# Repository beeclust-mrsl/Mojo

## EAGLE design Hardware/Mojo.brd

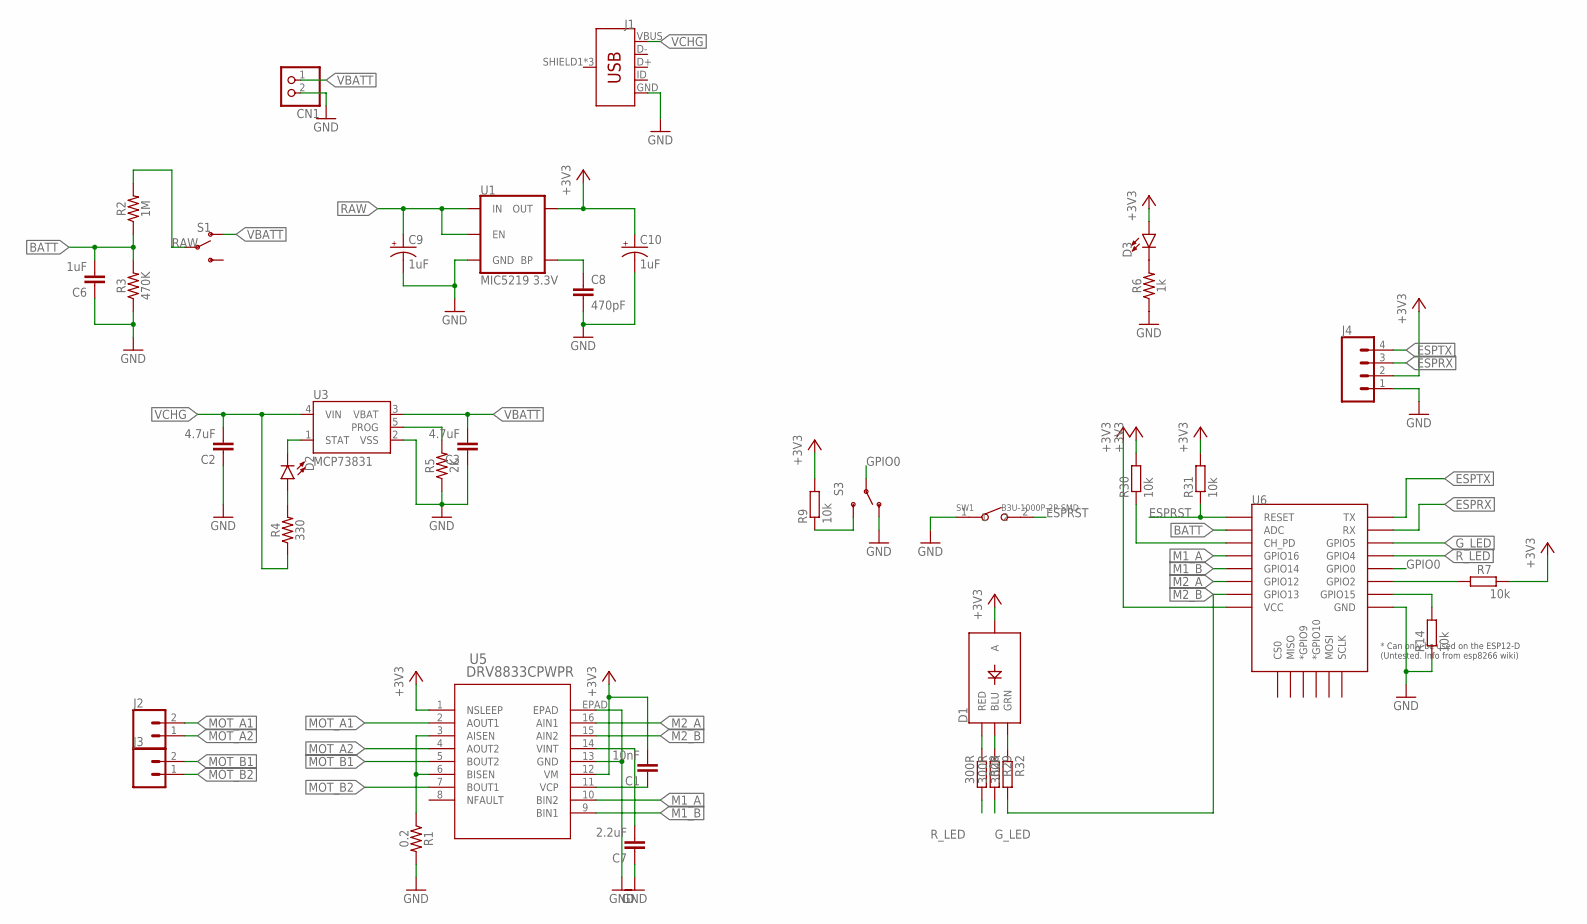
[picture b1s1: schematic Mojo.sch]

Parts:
C1: 10nF; C0603
C2, C3: 4.7uF; C0603
C6: 1uF; C0603
C7: 2.2uF; C0603
C8: 470pF; 0603
C9, C10: 1uF; EIA3216
CN1: JST_2PIN-THM-RA; JST-PH-2-THM-RA
D1: LED-RGB-CASMD; LED-TRICOLOR-SMD
D2, D3: LED0603; LED-0603
J1: USB_MICRO-BREDUCED_PASTE; USB-B-MICRO-SMD_RED_PASTE
J2, J3: CONN_02; 1X02
J4: CONN_04; 1X04
R1: 0.2; 0603
R2: 1M; 0603
R3: 470K; 0603
R4: 330; 0603
R5: 2K; 0603
R6: 1k; 0603
R7, R9, R14, R30, R31: 10k; R0603
R28, R29, R32: 300R; R0603
S1: SWITCH-SPDT-SMD-RIGHT-ANGLE; SWITCH_SPST_SMD_A
S3: SWITCH-SPDT-SMD-A; SWITCH-SPST-SMD-A
SW1: B3U-1000P-2P-SMD; SW2-2.6-3.0X2.5X1.2+0.4MM
U1: MIC5219 3.3V; SOT23-5
U3: MCP73831; SOT23-5
U5: DRV8833CPWPR; PWP16_2P31X2P46
U6: ESP12ESMD; ESP12E-SMD

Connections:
+3V3: C1.2, C10.+, D1.A, D3.A, J4.2, R7.2, R9.2, R30.2, R31.2, U1.5 (OUT), U5.1 (NSLEEP), U5.12 (VM), U6.VCC
BATT: C6.2, R2.1, R3.2, U6.ADC
ESPRST: R31.1, SW1.2, U6.RESET
ESPRX: J4.3, U6.RXD0 (RX)
ESPTX: J4.4, U6.TXD0 (TX)
GND: C2.1, C3.1, C6.1, C7.1, C8.2, C9.-, C10.-, CN1.2 (1), J1.GND, J4.1, R1.2, R3.1, R5.1, R6.1, R14.1, S3.1 (O), SW1.1, U1.2 (GND), U3.2 (VSS), U5.13 (GND), U5.EPAD, U6.GND
GPIO0: S3.2, U6.GPIO0
G_LED: R29.2, U6.GPIO5
M1_A: U5.10 (BIN2), U6.GPIO16
M1_B: U5.9 (BIN1), U6.GPIO14
M2_A: U5.16 (AIN1), U6.GPIO12
M2_B: R32.2, U5.15 (AIN2), U6.GPIO13
MOT_A1: J2.2, U5.2 (AOUT1)
MOT_A2: J2.1, U5.4 (AOUT2)
MOT_B1: J3.2, U5.5 (BOUT2)
MOT_B2: J3.1, U5.7 (BOUT1)
unnamed: R9.1, S3.3 (S)
unnamed: D3.C, R6.2
unnamed: D2.C, U3.1 (STAT)
unnamed: D2.A, R4.2
unnamed: C8.1, U1.4 (BP)
unnamed: R5.2, U3.5 (PROG)
unnamed: R1.1, U5.3 (AISEN), U5.6 (BISEN)
unnamed: C7.2, U5.14 (VINT)
unnamed: C1.1, U5.11 (VCP)
unnamed: R30.1, U6.CH_PD
unnamed: D1.R (RED), R28.1
unnamed: D1.B (BLU), R29.1
unnamed: D1.G (GRN), R32.1
unnamed: R14.2, U6.GPIO15
RAW: C9.+, R2.2, S1.2, U1.1 (IN), U1.3 (EN)
R_LED: R28.2, U6.GPIO4
SDAESP: R7.1, U6.GPIO2
VBATT: C3.2, CN1.1 (2), S1.1 (O), U3.3 (VBAT)
VCHG: C2.2, J1.VBUS, R4.1, U3.4 (VIN)

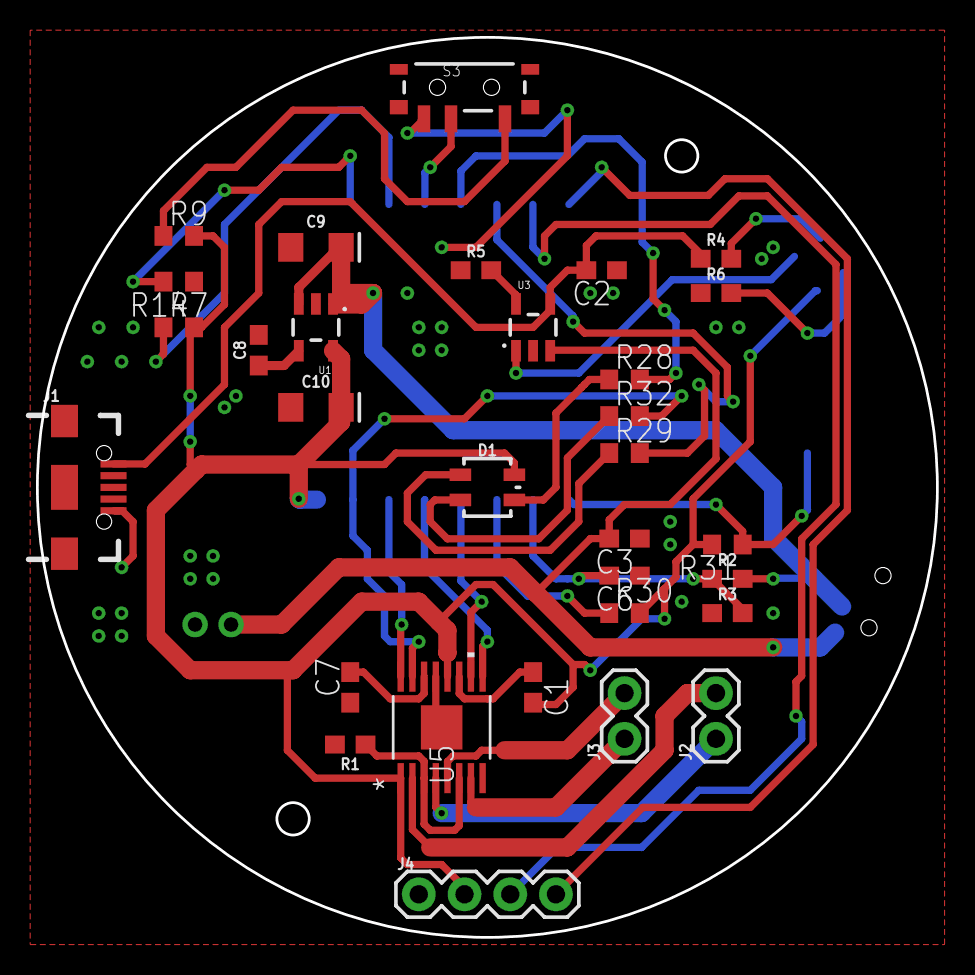
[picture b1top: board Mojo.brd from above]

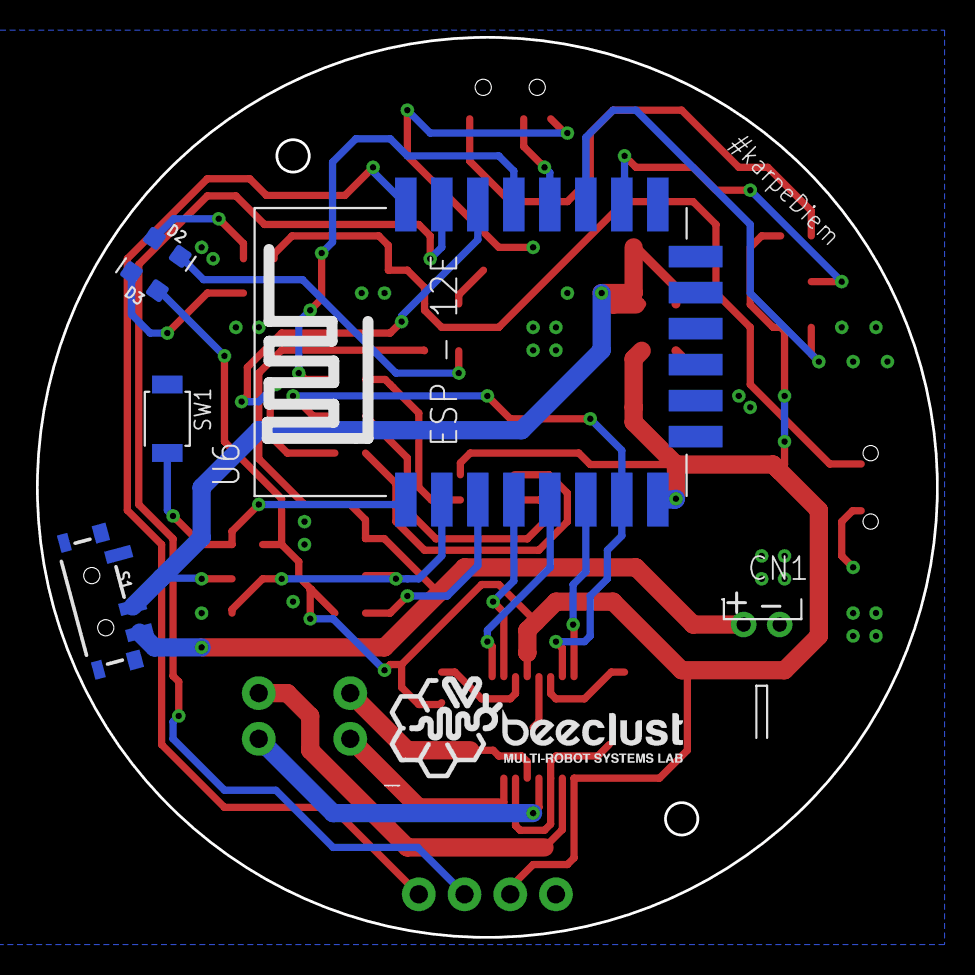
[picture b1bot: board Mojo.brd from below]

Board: 2 copper layers, 50.0 x 50.0 mm, 38 parts (7 on the bottom side), 35 nets.

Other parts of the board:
U$1: LOGO-M

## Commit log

2021-03-19 Restructured File System

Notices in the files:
parts and their libraries:
SparkFun-Capacitors: Licensing: Creative Commons ShareAlike 4.0 International - https://creativecommons.org/licenses/by-sa/4.0
